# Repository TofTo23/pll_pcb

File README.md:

# Project of PLL

This repository covers designing the PLL schematic (LTSpice), creating the PCB layout, soldering and testing. Furthermore, there is the simple 3D model of case printed using 3D printer.

<div style="display: flex; gap: 10px;">

</div>

<div style="display: flex; gap: 10px;">

</div>

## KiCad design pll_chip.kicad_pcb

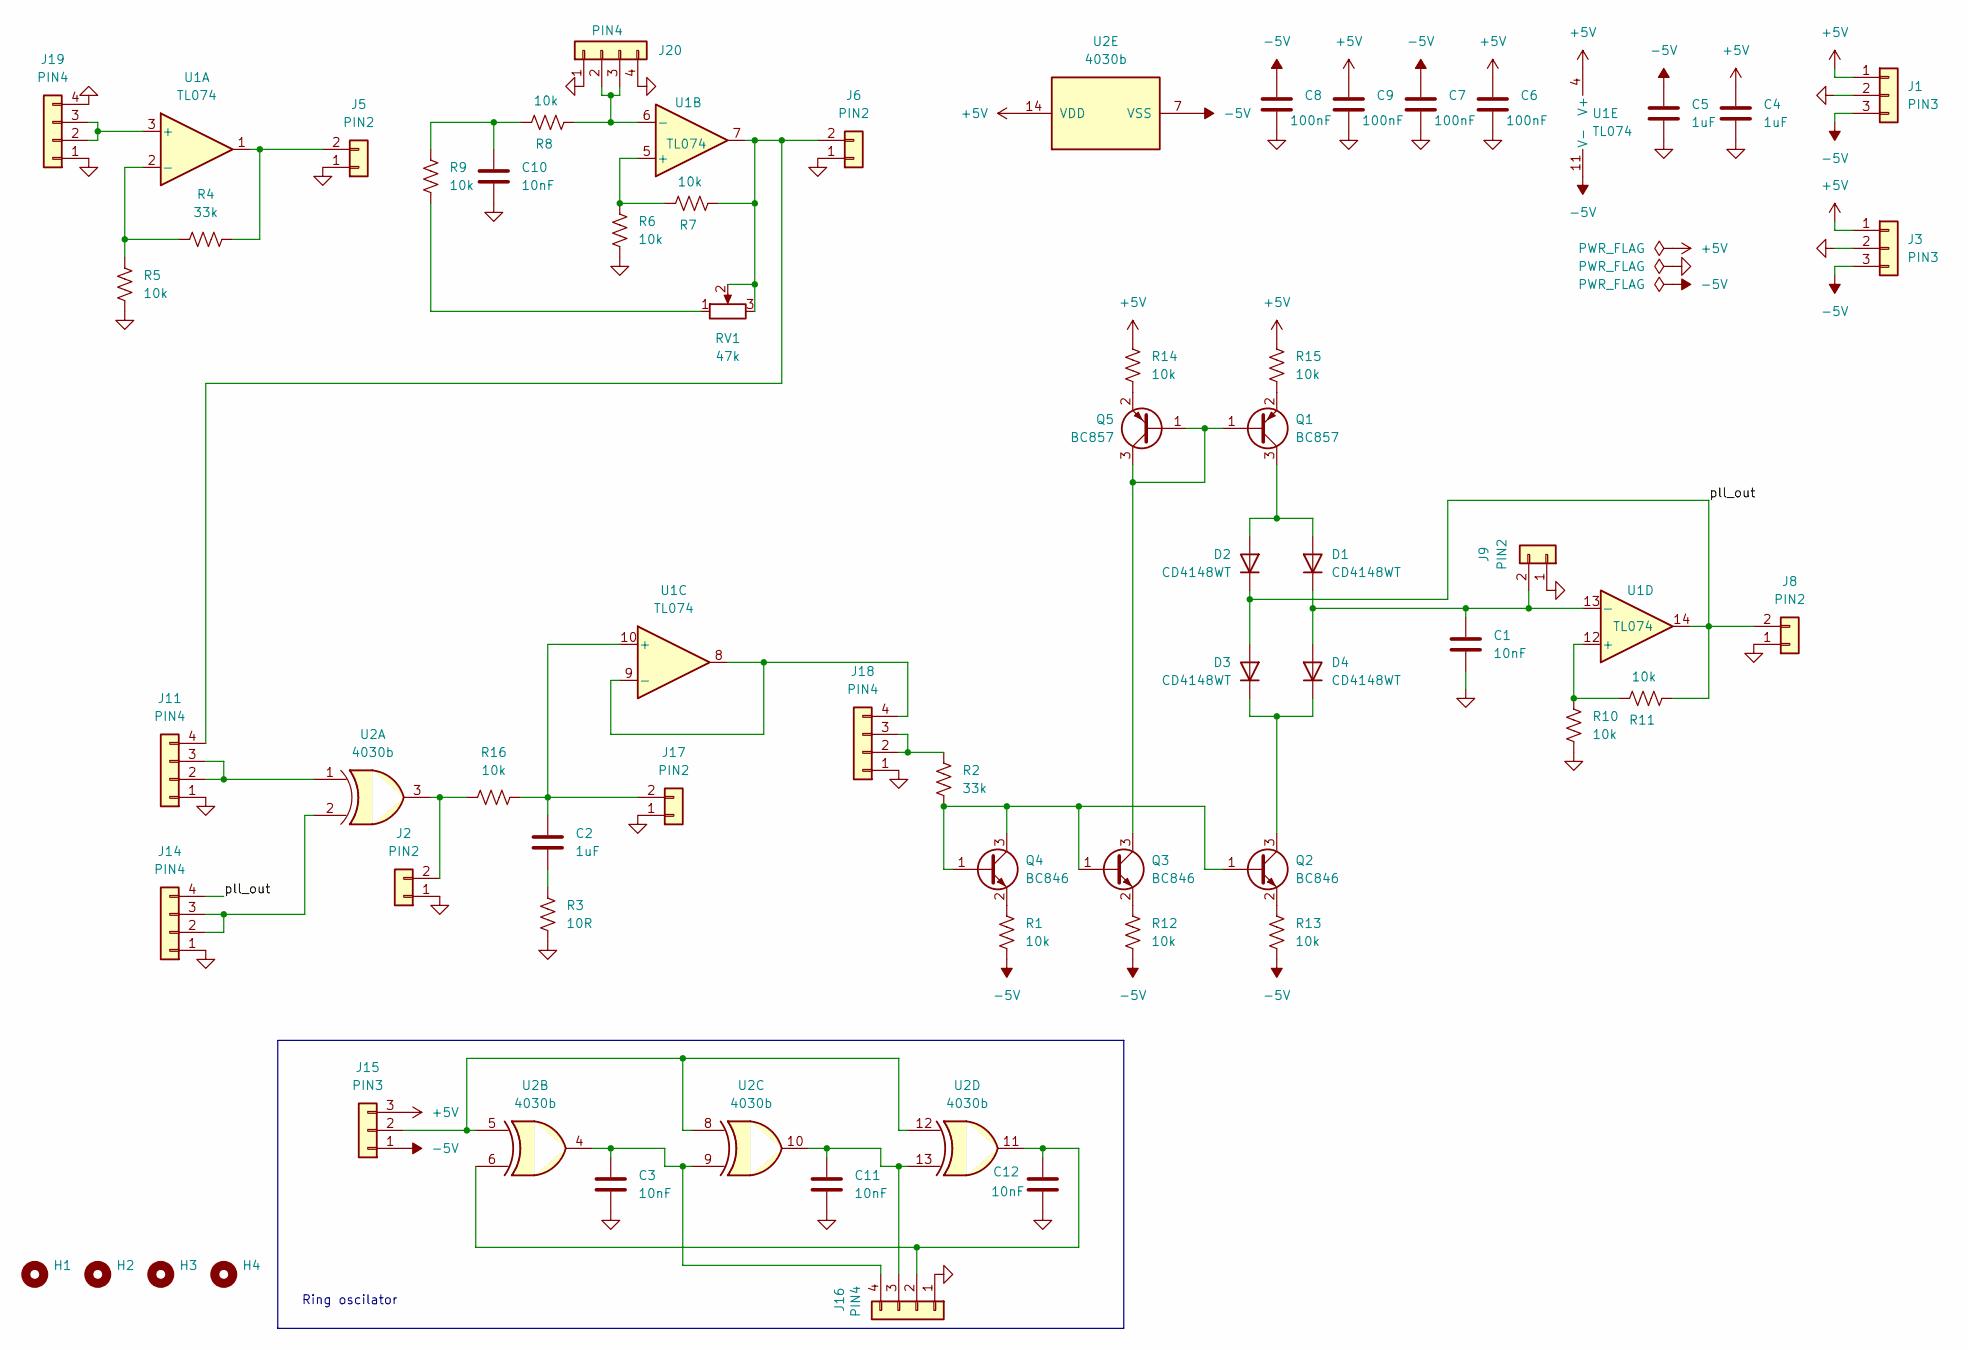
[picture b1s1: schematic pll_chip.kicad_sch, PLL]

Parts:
C1, C3, C10, C11, C12: 10nF; C_0603_1608Metric
C2, C4, C5: 1uF; C_0603_1608Metric
C6, C7, C8, C9: 100nF; C_0603_1608Metric
D1, D2, D3, D4: CD4148WT; D_0603_1608Metric
H1, H2, H3, H4: MountingHole; MountingHole_3.2mm_M3_DIN965
J1, J3, J15: PIN3; PinHeader_1x03_P2.54mm_Vertical
J2, J5, J6, J8, J9, J17: PIN2; PinHeader_1x02_P2.54mm_Vertical
J11, J14, J16, J18, J19, J20: PIN4; PinHeader_1x04_P2.54mm_Vertical
Q1, Q5: BC857; SOT-23
Q2, Q3, Q4: BC846; SOT-23
R1, R5, R6, R7, R8, R9, R10, R11, R12, R13, R14, R15, R16: 10k; R_0603_1608Metric
R2, R4: 33k; R_0603_1608Metric
R3: 10R; R_0603_1608Metric
RV1: 47k; Potentiometer_ACP_CA14V-15_Vertical
U1: TL074; SOIC-14_3.9x8.7mm_P1.27mm
U2: 4030b; SOIC-14_3.9x8.7mm_P1.27mm

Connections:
+5V: C4.1, C6.1, C9.1, J1.1, J3.1, J15.3, R14.1, R15.1, U1.4 (V+), U2.14 (VDD)
-5V: C5.1, C7.1, C8.1, J1.3, J3.3, J15.1, R1.2, R12.2, R13.2, U1.11 (V-), U2.7 (VSS)
/pll_out: D2.1 (K), D3.2 (A), J8.2, J14.4, R11.2, U1.14
GND: C1.2, C3.2, C4.2, C5.2, C6.2, C7.2, C8.2, C9.2, C10.2, C11.2, C12.2, J1.2, J2.1, J3.2, J5.1, J6.1, J8.1, J9.1, J11.1, J14.1, J16.1, J17.1, J18.1, J19.1, J19.4, J20.1, J20.4, R3.2, R5.2, R6.2, R10.2
unnamed: C2.2, R3.1
unnamed: C10.1, R8.1, R9.1
unnamed: D1.2 (A), D2.2 (A), Q1.3 (C)
unnamed: C1.1, D1.1 (K), D4.2 (A), J9.2, U1.13 (-)
unnamed: D3.1 (K), D4.1 (K), Q2.3 (C)
unnamed: J2.2, R16.1, U2.3
unnamed: J5.2, R4.2, U1.1
unnamed: J11.2, J11.3, U2.1
unnamed: J6.2, J11.4, R7.2, RV1.2, RV1.3, U1.7
unnamed: J14.2, J14.3, U2.2
unnamed: J15.2, U2.5, U2.8, U2.12
unnamed: C12.1, J16.2, U2.6, U2.11
unnamed: C11.1, J16.3, U2.10, U2.13
unnamed: C3.1, J16.4, U2.4, U2.9
unnamed: C2.1, J17.2, R16.2, U1.10 (+)
unnamed: J18.2, J18.3, R2.1
unnamed: J18.4, U1.8, U1.9 (-)
unnamed: J19.2, J19.3, U1.3 (+)
unnamed: J20.2, J20.3, R8.2, U1.6 (-)
unnamed: Q1.1 (B), Q3.3 (C), Q5.1 (B), Q5.3 (C)
unnamed: Q1.2 (E), R15.2
unnamed: Q2.1 (B), Q3.1 (B), Q4.1 (B), Q4.3 (C), R2.2
unnamed: Q2.2 (E), R13.1
unnamed: Q3.2 (E), R12.1
unnamed: Q4.2 (E), R1.1
unnamed: Q5.2 (E), R14.2
unnamed: R9.2, RV1.1
unnamed: R4.1, R5.1, U1.2 (-)
unnamed: R6.1, R7.1, U1.5 (+)
unnamed: R10.1, R11.1, U1.12 (+)

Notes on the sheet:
Ring oscilator

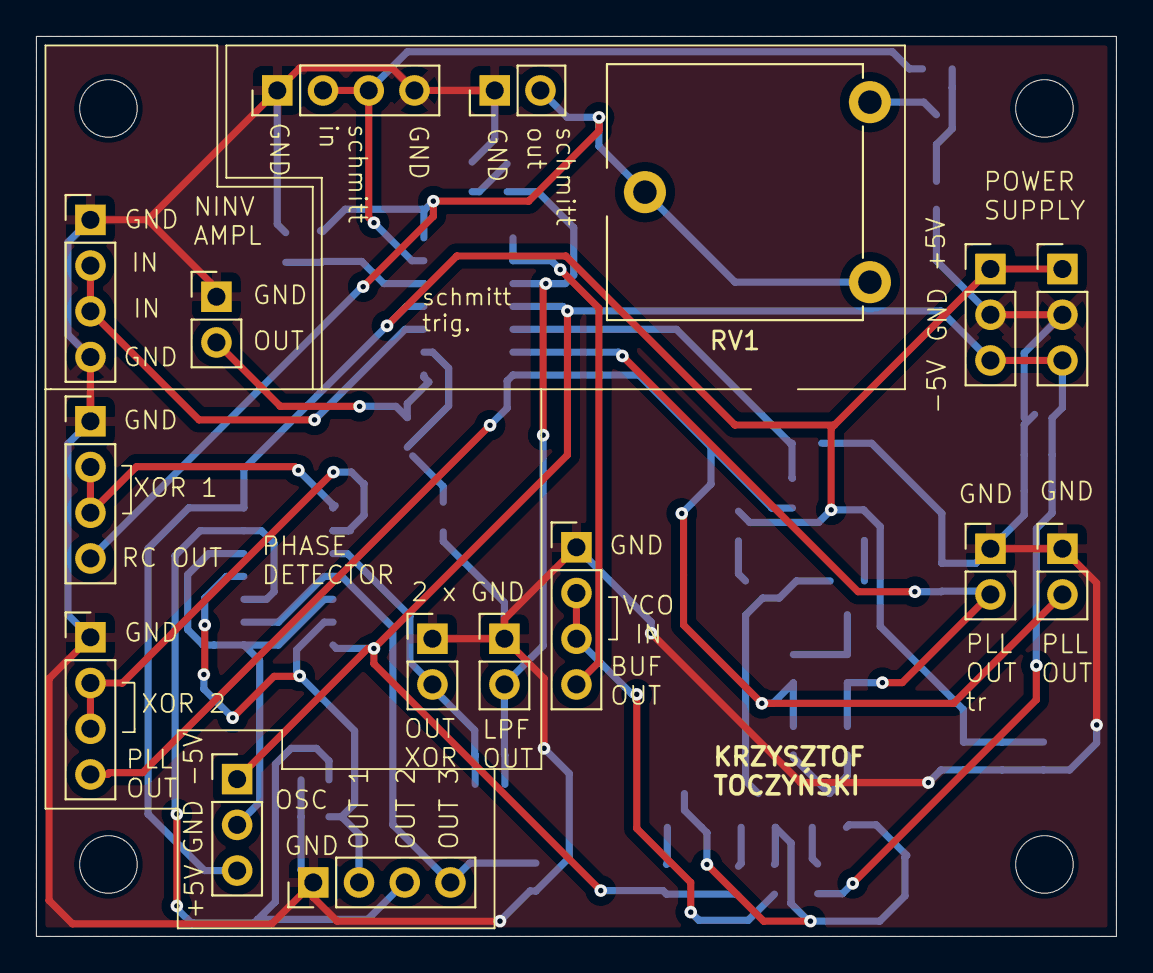
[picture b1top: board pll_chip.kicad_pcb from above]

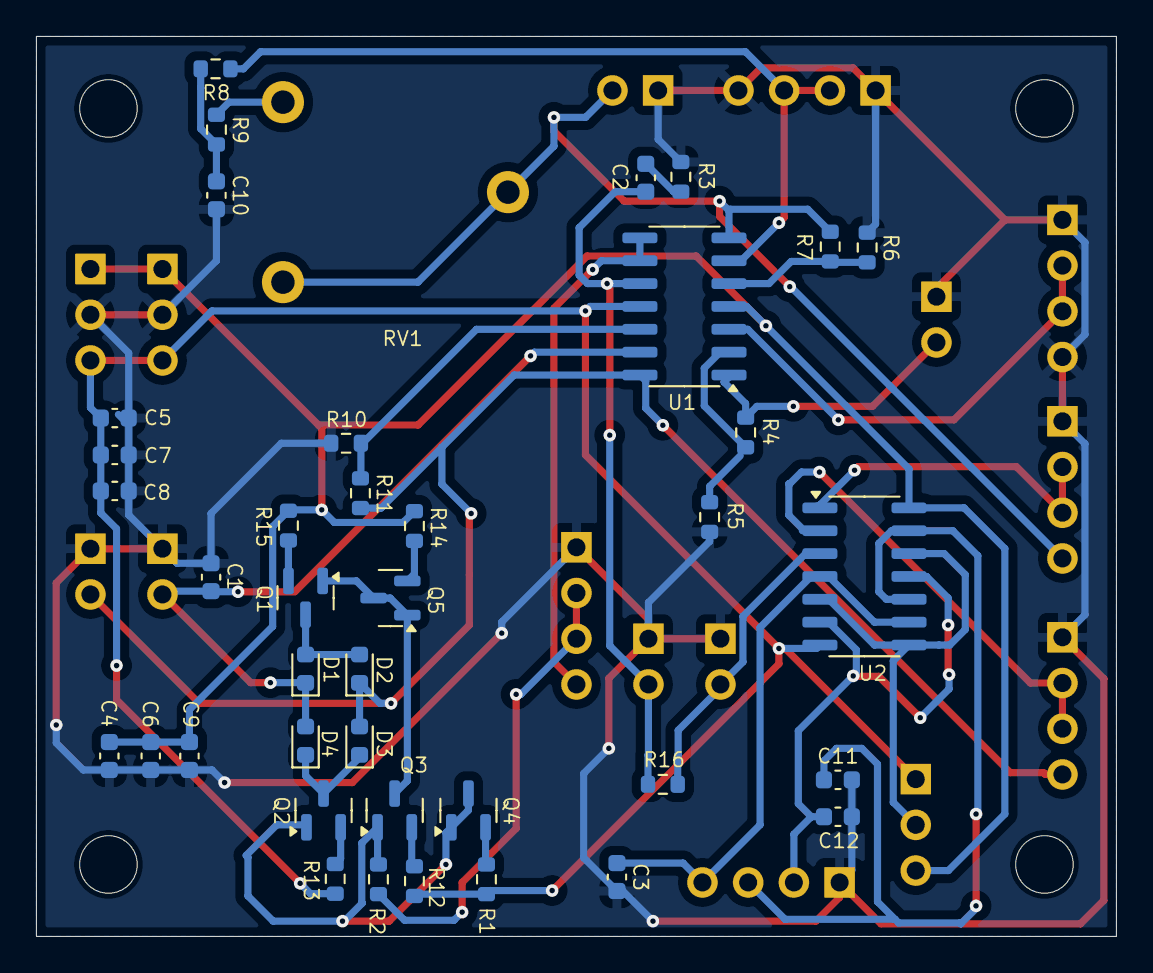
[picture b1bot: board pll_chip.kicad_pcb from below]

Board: 2 copper layers, 60.0 x 50.0 mm, 59 parts (39 on the bottom side), 34 nets.

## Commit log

2026-03-18 add kicad schema
2026-03-18 add pictures
2026-03-18 pictures v2
2026-03-18 pictures v3
2026-03-18 Initialize README with project details and images
    Added project overview and images to README.
2026-03-18 add picture
